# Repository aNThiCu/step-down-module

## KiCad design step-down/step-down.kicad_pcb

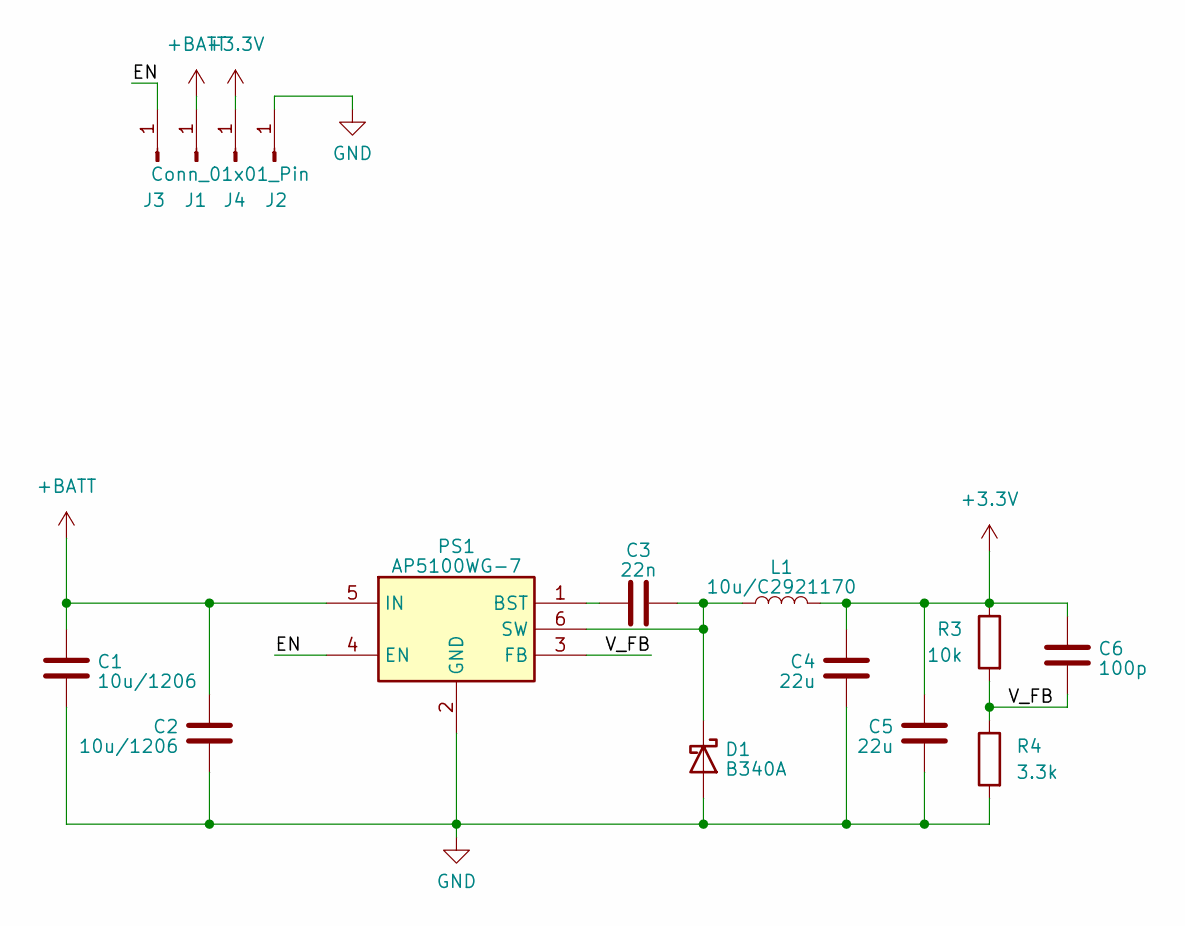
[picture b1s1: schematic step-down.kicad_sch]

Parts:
C1, C2: 10u/1206; C_0603_1608Metric; MPN C13585
C3: 22n; C_0603_1608Metric; MPN C21122
C4, C5: 22u; C_0603_1608Metric; MPN C45783
C6: 100p; C_0603_1608Metric; MPN C1790
D1: B340A; D_SMA; MPN C3018525
J1, J2, J3, J4: Conn_01x01_Pin; PinSocket_1x01_P2.54mm_Vertical
L1: 10u/C2921170; L_Chilisin_BMRA00040420; MPN C2921170
PS1: AP5100WG-7; SOT95P285X140-6N; Mouser Part Number 621-AP5100WG-7
R3: 10k; R_0603_1608Metric; MPN C25804
R4: 3.3k; R_0603_1608Metric; MPN C22975

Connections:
+3.3V: C4.1, C5.1, C6.1, J4.1, L1.2, R3.1
+BATT: C1.1, C2.1, J1.1, PS1.5 (IN)
/EN: J3.1, PS1.4 (EN)
/V_FB: C6.2, PS1.3 (FB), R3.2, R4.1
GND: C1.2, C2.2, C4.2, C5.2, D1.2 (A), J2.1, PS1.2 (GND), R4.2
unnamed: C3.2, D1.1 (K), L1.1, PS1.6 (SW)
unnamed: C3.1, PS1.1 (BST)

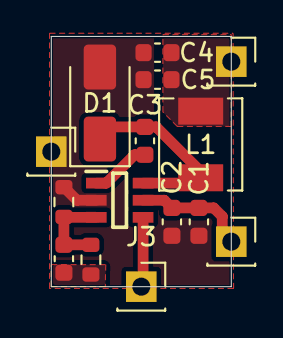
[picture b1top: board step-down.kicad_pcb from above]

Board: 2 copper layers, 10.0 x 13.9 mm, 15 parts (0 on the bottom side), 7 nets.

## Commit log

2025-07-14 done
2025-07-14 moved EN logic to external control
